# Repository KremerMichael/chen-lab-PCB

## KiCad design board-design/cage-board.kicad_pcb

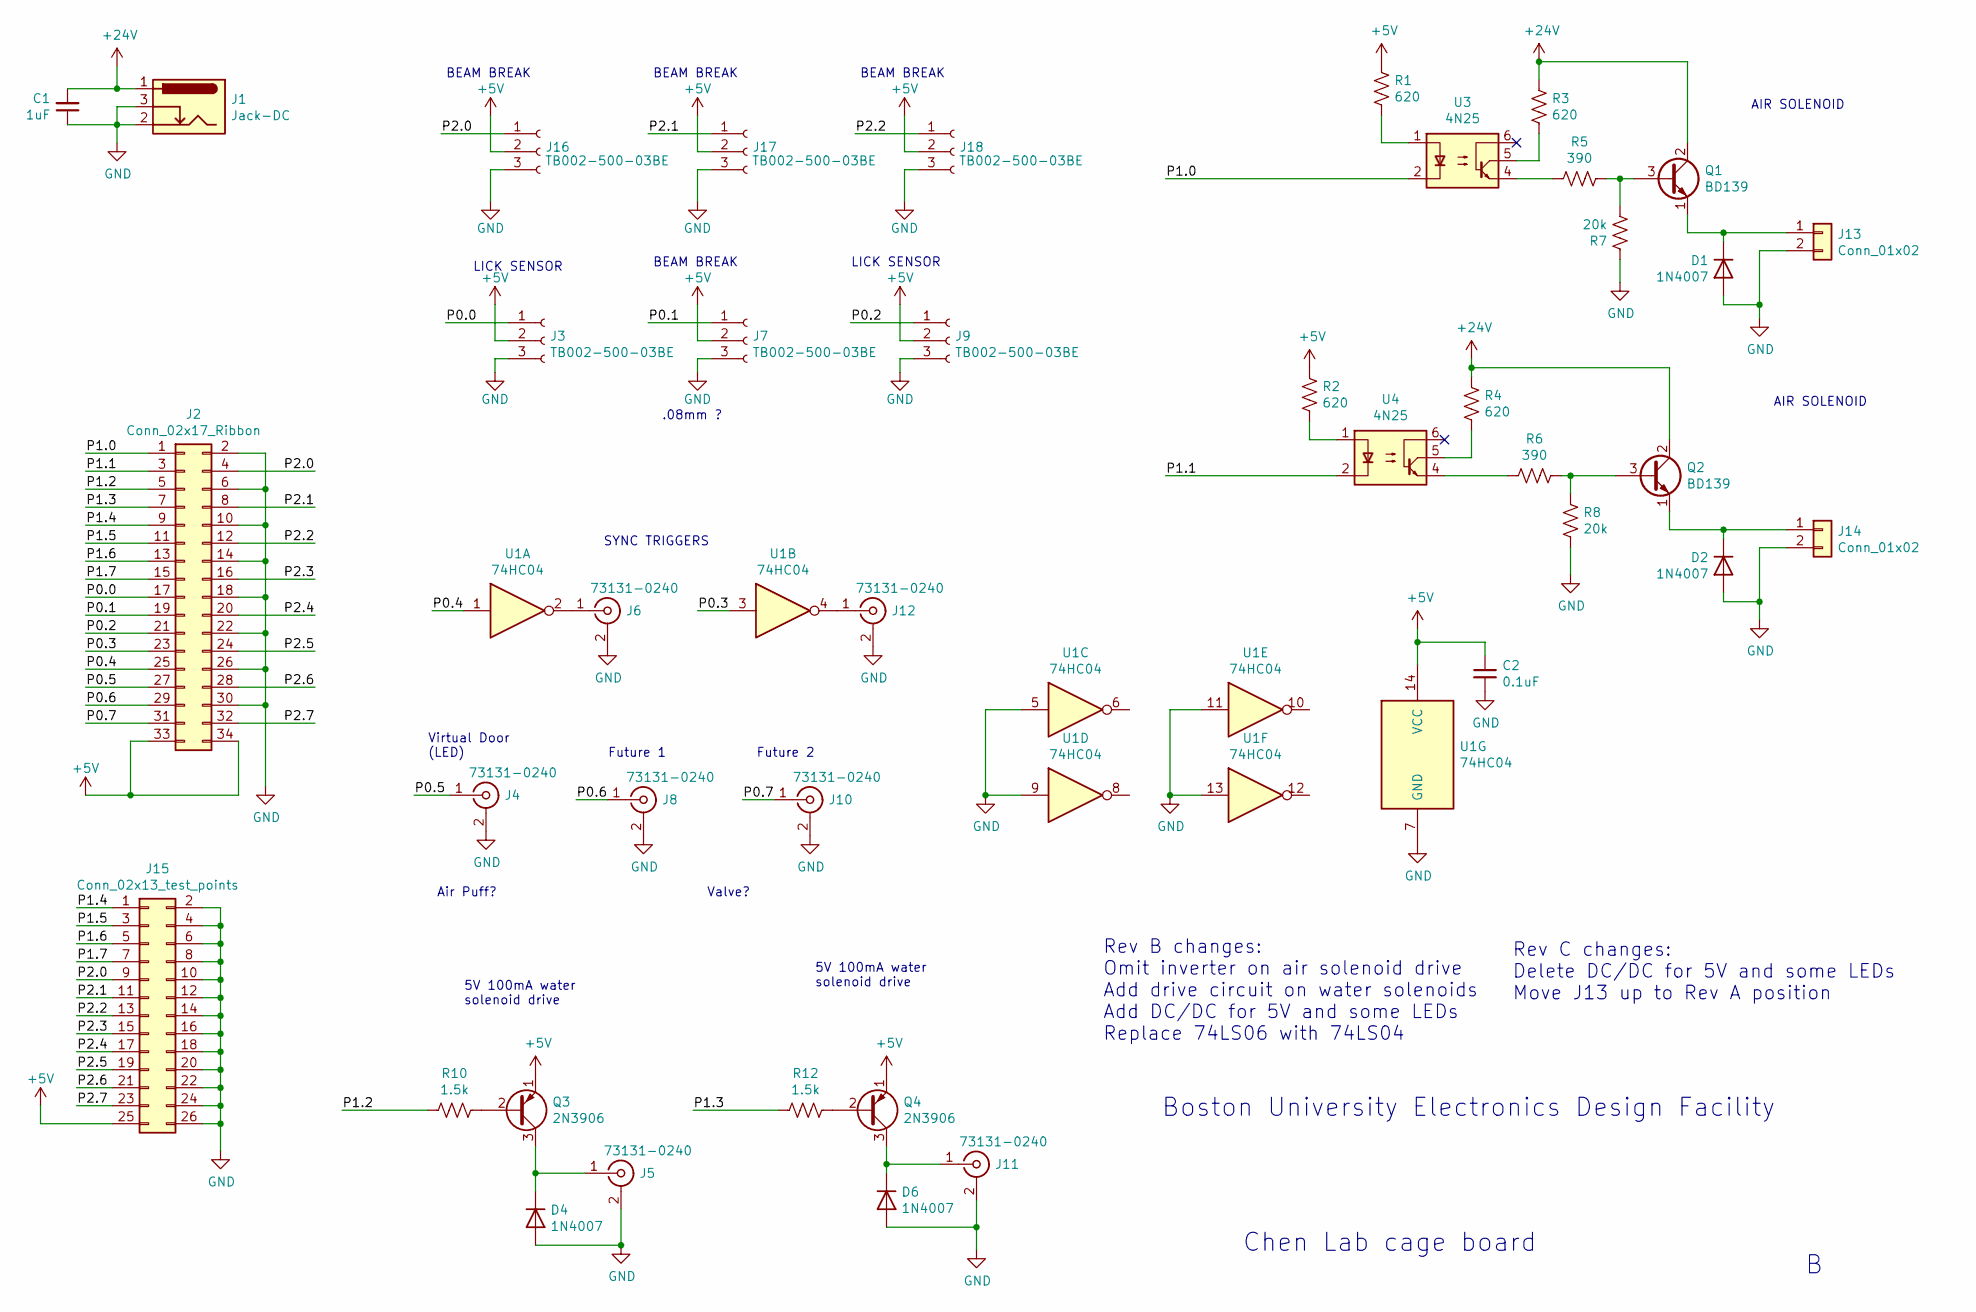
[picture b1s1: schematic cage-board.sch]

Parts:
C1: 1uF; C_0805_2012Metric_Pad1.15x1.40mm_HandSolder
C2: 0.1uF; C_0805_2012Metric_Pad1.15x1.40mm_HandSolder
D1, D2, D4, D6: 1N4007; D_DO-41_SOD81_P10.16mm_Horizontal
J1: Jack-DC; BarrelJack_Horizontal
J2: Conn_02x17_Ribbon; PinHeader_2x17_P2.54mm_Vertical
J3, J7, J9, J16, J17, J18: TB002-500-03BE; TerminalBlock_bornier-3_P5.08mm
J4, J5, J6, J8, J10, J11, J12: 73131-0240; BNC-Chen
J13, J14: Conn_01x02; TerminalBlock_bornier-2_P5.08mm
J15: Conn_02x13_test_points; PinHeader_2x13_P2.54mm_Vertical
Q1, Q2: BD139; TO-126-3_Vertical
Q3, Q4: 2N3906; TO-92_Inline
R1, R2, R3, R4: 620; R_0805_2012Metric_Pad1.15x1.40mm_HandSolder
R5, R6: 390; R_0805_2012Metric_Pad1.15x1.40mm_HandSolder
R7, R8: 20k; R_0805_2012Metric_Pad1.15x1.40mm_HandSolder
R10, R12: 1.5k; R_0805_2012Metric_Pad1.20x1.40mm_HandSolder
U1: 74HC04; DIP-14_W7.62mm_Socket_LongPads
U3, U4: 4N25; DIP-6_W7.62mm

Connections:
+5V: C2.1, J2.33, J2.34, J3.2, J7.2, J9.2, J15.25, J16.2, J17.2, J18.2, Q3.1 (E), Q4.1 (E), R1.2, R2.2, U1.14 (VCC)
+24V: C1.2, J1.1, Q1.2 (C), Q2.2 (C), R3.2, R4.2
/P0.0: J2.17, J3.1
/P0.1: J2.19, J7.1
/P0.2: J2.21, J9.1
/P0.3: J2.23, U1.3
/P0.4: J2.25, U1.1
/P0.5: J2.27, J4.1 (In)
/P0.6: J2.29, J8.1 (In)
/P0.7: J2.31, J10.1 (In)
/P1.0: J2.1, U3.2
/P1.1: J2.3, U4.2
/P1.2: J2.5, R10.2
/P1.3: J2.7, R12.2
/P1.4: J2.9, J15.1
/P1.5: J2.11, J15.3
/P1.6: J2.13, J15.5
/P1.7: J2.15, J15.7
/P2.0: J2.4, J15.9, J16.1
/P2.1: J2.8, J15.11, J17.1
/P2.2: J2.12, J15.13, J18.1
/P2.3: J2.16, J15.15
/P2.4: J2.20, J15.17
/P2.5: J2.24, J15.19
/P2.6: J2.28, J15.21
/P2.7: J2.32, J15.23
GND: C1.1, C2.2, D1.2 (A), D2.2 (A), D4.2 (A), D6.2 (A), J1.2, J1.3, J2.2, J2.6, J2.10, J2.14, J2.18, J2.22, J2.26, J2.30, J3.3, J4.2 (Ext), J5.2 (Ext), J6.2 (Ext), J7.3, J8.2 (Ext), J9.3, J10.2 (Ext), J11.2 (Ext), J12.2 (Ext), J13.2, J14.2, J15.2, J15.4, J15.6, J15.8, J15.10, J15.12, J15.14, J15.16, J15.18, J15.20, J15.22, J15.24, J15.26, J16.3, J17.3, J18.3, R7.2, R8.1, U1.5, U1.7 (GND), U1.9, U1.11, U1.13
unnamed: D1.1 (K), J13.1, Q1.1 (E)
unnamed: D2.1 (K), J14.1, Q2.1 (E)
unnamed: D4.1 (K), J5.1 (In), Q3.3 (C)
unnamed: D6.1 (K), J11.1 (In), Q4.3 (C)
unnamed: J6.1 (In), U1.2
unnamed: J12.1 (In), U1.4
unnamed: Q1.3 (B), R5.1, R7.1
unnamed: Q2.3 (B), R6.1, R8.2
unnamed: Q3.2 (B), R10.1
unnamed: Q4.2 (B), R12.1
unnamed: R1.1, U3.1
unnamed: R2.1, U4.1
unnamed: R3.1, U3.5
unnamed: R4.1, U4.5
unnamed: R5.2, U3.4
unnamed: R6.2, U4.4

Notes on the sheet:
LICK SENSOR
BEAM BREAK
SYNC TRIGGERS
Virtual Door (LED)
Future 1
Future 2
Air Puff?
Valve?
AIR SOLENOID
.08mm ?
Chen Lab cage board
Boston University Electronics Design Facility
Rev B changes: Omit inverter on air solenoid drive Add drive circuit on water solenoids Add DC/DC for 5V and some LEDs Replace 74LS06 with 74LS04
5V 100mA water solenoid drive
Rev C changes: Delete DC/DC for 5V and some LEDs Move J13 up to Rev A position

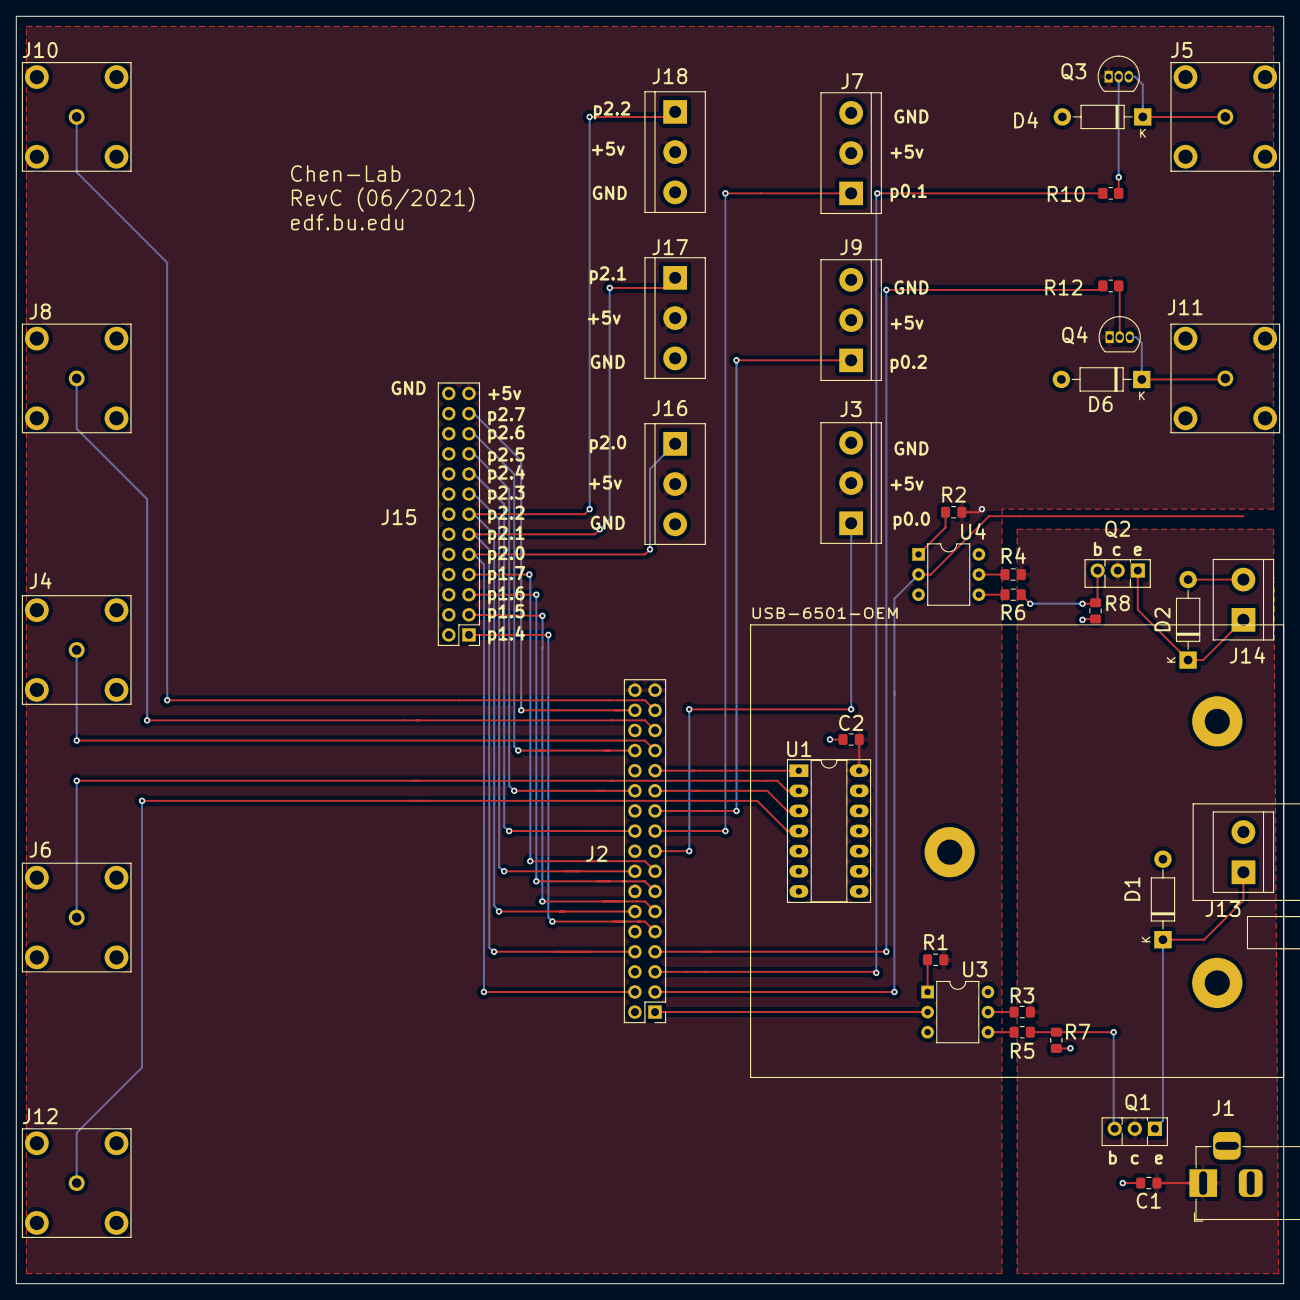
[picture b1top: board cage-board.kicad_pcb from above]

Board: 2 copper layers, 160.0 x 160.0 mm, 42 parts (0 on the bottom side), 43 nets.

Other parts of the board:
USB-6501-OEM: usb-6501-oem

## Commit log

2020-08-23 started git repo
2020-08-24 auto push run at Mon 24 Aug 2020 01:14:17 AM EDT
2020-08-24 auto push run at Mon 24 Aug 2020 11:25:32 AM EDT
2020-08-24 auto push run at Mon 24 Aug 2020 11:52:34 AM EDT
2020-08-24 auto push run at Mon 24 Aug 2020 11:56:28 AM EDT
2020-08-24 auto push run at Mon 24 Aug 2020 11:58:40 AM EDT
2020-08-24 auto push run at Mon 24 Aug 2020 12:03:22 PM EDT
2020-08-24 auto push run at Mon 24 Aug 2020 12:08:45 PM EDT
2020-08-24 auto push run at Mon 24 Aug 2020 12:14:02 PM EDT
2020-08-24 auto push run at Mon 24 Aug 2020 03:08:45 PM EDT
2020-08-24 auto push run at Mon 24 Aug 2020 03:10:38 PM EDT
2020-08-25 moving to kicad
2020-08-26 auto push run at Tue 25 Aug 2020 09:51:00 PM EDT
2020-08-26 auto push run at Tue 25 Aug 2020 09:53:13 PM EDT
2020-08-26 Add some 3D models
2020-08-26 more 3D models
2020-08-27 3D model for USB thing
2020-08-27 Add USB board with 3D
2020-08-27 Raise USB board to 0.75in height
2020-09-02 moved screw terminals and updated test points
2020-09-02 fixing schematic notes
2020-09-02 added BoM
2020-09-02 fixing 3d models hopefully
2020-09-03 added inch to board length and spaced out connectors more
2020-09-08 adding protocase files
2020-09-09 adding dimensions for protocase
2020-09-09 working on finishing enclosure
2020-09-16 working on resizing board
2020-09-17 working on fixing connectors
2020-09-17 moving stuff around and working on enclosure
2020-09-20 Finished cuts for panels
2020-09-23 adding BoM's for one off parts
2020-09-24 fixing BoM
2020-11-19 add revision docs
2020-12-02 Add ECO list
2020-12-02 add photo RevA
2020-12-02 edit ECOs
2020-12-02 Rev B mods
2020-12-02 Rev B changes to sch done?
2021-01-05 updating schematic, and moving PCB layout forward to RevB
2021-04-09 auto push run at Fri Apr 9 11:10:50 EDT 2021
2021-04-09 driver doc
2021-04-09 auto push run at Fri Apr 9 12:23:24 EDT 2021
2021-04-16 changin to right angle LEDs, fixing terminal blocks, fixing DC-DC footprint
2021-04-16 fixing 5v led
2021-04-23 auto push run at Fri Apr 23 09:52:58 EDT 2021
2021-04-23 new BoM
2021-04-27 migrating to branch with new BNC
2021-05-31 all done except moving J13
2021-05-31 Final Rev C layout
2021-05-31 Candidate Rev C gerbers
2021-05-31 Restore USB board footprint, tweak silkscreen
2021-06-09 Add Rev C BOM
2021-06-09 Final Rev C gerbers
2021-06-09 Fix a couple of BOM issues
